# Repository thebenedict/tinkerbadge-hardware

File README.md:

# Tinker Badge hardware

Open **tinkerbadge.kicad_pro** in KiCad 10. The root schematic links to power, processor, display, lighting and peripheral sheets.

- [Specification](docs/spec.md)
- [Current schematic decisions and remaining gates](docs/design/implementation_status.md)
- [Design review, 10 November 2026](docs/design/design_review_2026-11-10.md)
- [Independent review, 11 November 2026](docs/review/design_review_2026-11-11.md) and [the response with the revision 0.3 fixes](docs/review/response_2026-11-11.md)
- [JLCPCB release package and order settings](docs/design/jlcpcb_release.md); order files in `production/jlcpcb/`
- [Reviewed physical-pin assignments](docs/pinouts.md)
- [Verification results](docs/design/verification.md)
- [Planning BOM and source history](docs/AI_Tinkerers_Badge_Design_BOM_Draft_2026-11-09.md)

The first prototype uses a single nominal 3.3 V rail for logic and the eight RGB LEDs. Regulator tolerance can fall below the LED datasheet minimum, so startup, low-battery, radio and full-white load-step tests are required.

This is a development design. The battery is a two-wire protected pouch cell on a rear JST PH header; charging is enabled at about 270 mA with on-board thermistors. The [review response](docs/review/response_2026-11-11.md) lists what changed in board revision 0.3 and what still needs hardware in hand, starting with a dry-fit of the display flex.

## Repeat the electrical check

Export the complete root schematic netlist using KiCad CLI or the installed Konnect MCP, then run:

```
python3 tools/check_schematic_contracts.py path/to/export.net --output path/to/endpoint-result.json
python3 tools/check_schematic_properties.py path/to/export.net --output path/to/property-result.json
python3 tools/test_contract_checker.py
python3 tools/test_property_checker.py
python3 tools/test_alps_buttons.py
```

The checker compares every physical pin and intentional NC with the separately maintained reviewed block contracts. The separate property checker covers explicitly declared values, part numbers, ratings, population and library associations. Run root ERC and inspect fresh sheet renders as well. Current outputs are in `exports/`, with a six-page PDF and a pinned verification manifest. The one-time capture scripts are not idempotent rebuild commands; rerunning them blindly can duplicate objects. Initial electrical capture used Konnect MCP. The user-approved [outlined-block revision](docs/design/outlined_blocks_review.md) uses bounded native edits, independent visual review and complete before/after exported-netlist comparison.

## Licensing

- Original hardware and mechanical designs: **CERN-OHL-P-2.0**.
- Original software, tools and firmware: **Apache-2.0**.
- Original documentation and artwork: **CC-BY-4.0**.

See [the licensing map](LICENSE.md) and [full license texts](LICENSES/README.md). Generated exports retain their source licenses. [Third-party notices](docs/THIRD_PARTY_NOTICES.md) cover KiCad libraries and manufacturer material.

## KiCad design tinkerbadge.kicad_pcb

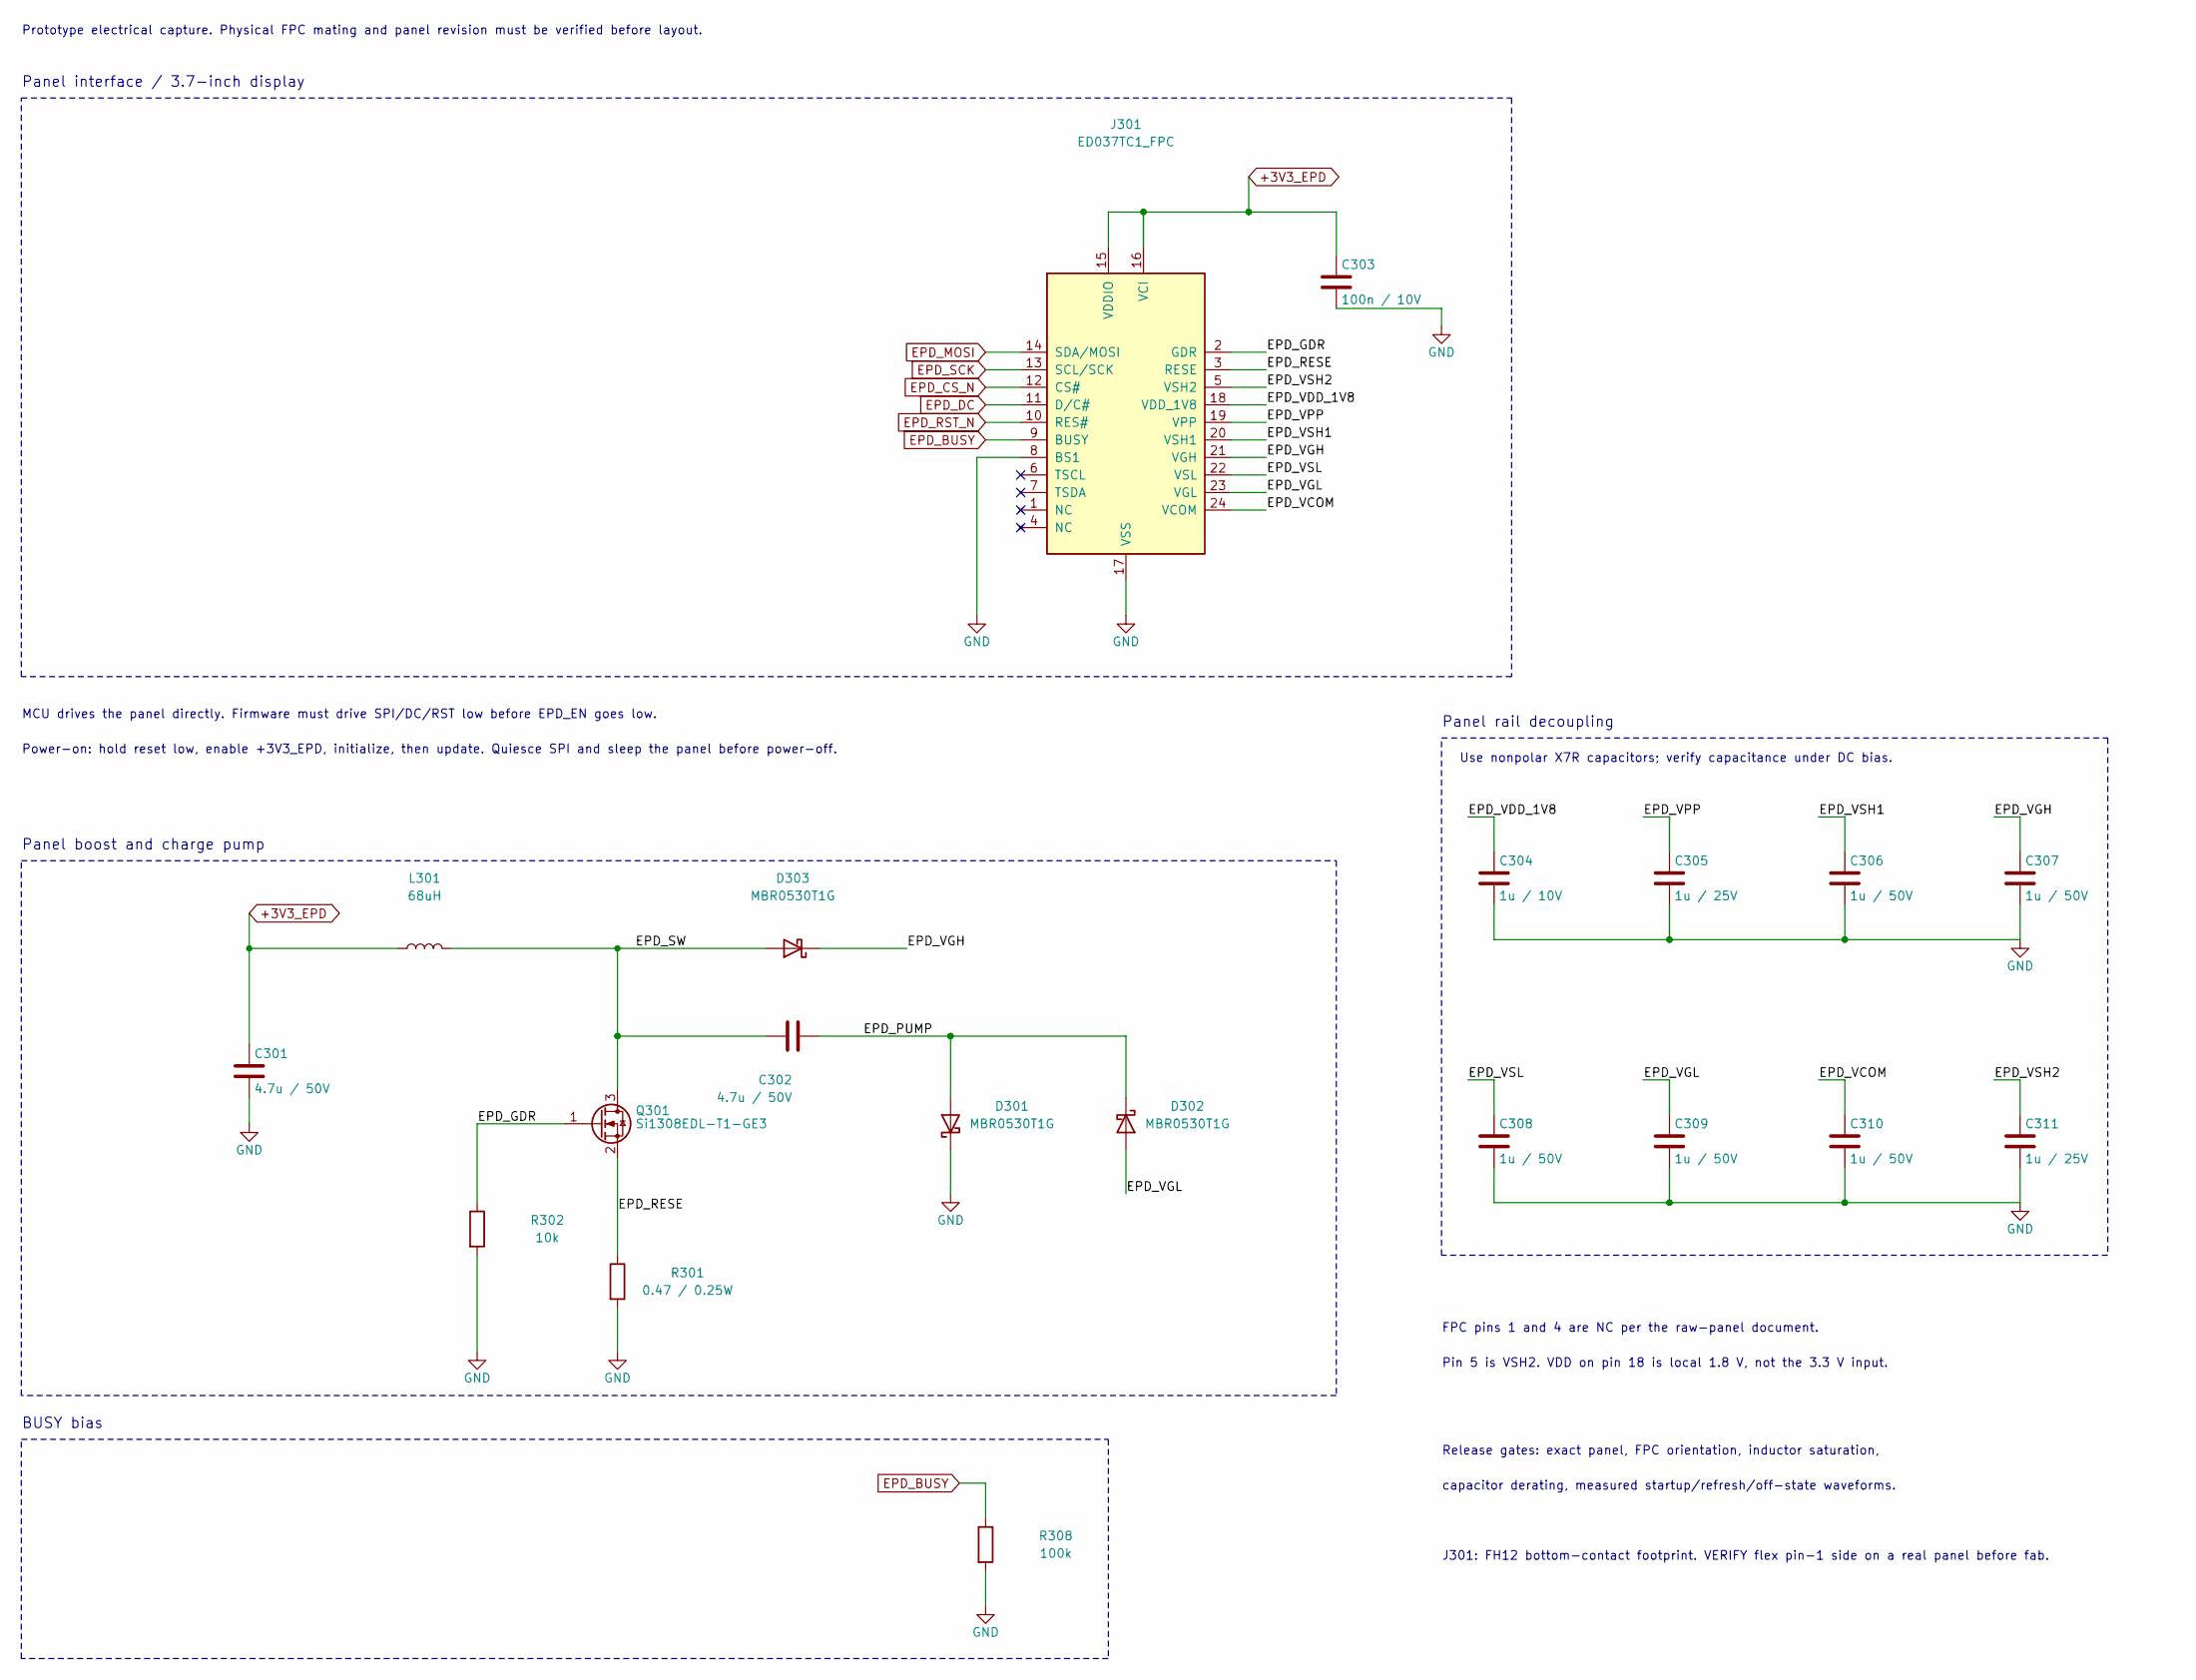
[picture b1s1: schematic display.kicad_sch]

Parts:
C301: 4.7u / 50V; C_1206_3216Metric; Rating 50V; X7R; ±10%; ceramic nonpolar; MPN 1206B475K500NT; LCSC C29823
C302: 4.7u / 50V; C_1206_3216Metric; Rating 50V; X7R; ±10%; ceramic nonpolar; verif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; MPN 1206B475K500NT; LCSC C29823
C303: 100n / 10V; C_0603_1608Metric; Rating 10V; X7R; ±10%; MPN CC0603KRX7R9BB104; LCSC C14663
C304: 1u / 10V; C_0805_2012Metric; Rating 10V; X7R; ±10%; ceramic nonpolar; selec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; MPN CL21B105KBFNNNE; LCSC C28323
C305, C311: 1u / 25V; C_0805_2012Metric; Rating 25V; X7R; ±10%; ceramic nonpolar; selec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; MPN CL21B105KBFNNNE; LCSC C28323
C306, C307, C308, C309, C310: 1u / 50V; C_0805_2012Metric; Rating 50V; X7R; ±10%; ceramic nonpolar; selec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; MPN CL21B105KBFNNNE; LCSC C28323
D301, D302, D303: MBR0530T1G; D_SOD-123; MPN MBR0530T1G; LCSC C82046
J301: ED037TC1_FPC; Hirose_FH12-24S-0.5SH_1x24-1MP_P0.50mm_Horizontal; MPN FH12-24S-0.5SH(55); LCSC C202112
L301: 68uH; L_Bourns-SRN4018; Rating ±20%; shielded; target Isat>=1A and Irm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; MPN SRN4018-680M; LCSC C2041717
Q301: Si1308EDL-T1-GE3; SOT-323_SC-70; MPN SI1308EDL-T1-GE3; LCSC C469327
R301: 0.47 / 0.25W; R_0805_2012Metric; Rating 1%; >=0.25W; pulse-rated; Kelvin route 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; MPN FBF05FT-R470-00L; LCSC C382278
R302: 10k; R_0603_1608Metric; Rating 1%; >=0.1W; MPN 0603WAF1002T5E; LCSC C25804
R308: 100k; R_0603_1608Metric; Rating 1%; >=0.1W; MPN 0603WAF1003T5E; LCSC C25803

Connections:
+3V3_EPD: C301.1, C303.1, J301.15 (VDDIO), J301.16 (VCI), L301.1; also elsewhere on the board
/03 E-PAPER DISPLAY/EPD_GDR: J301.2 (GDR), Q301.1 (G), R302.1
/03 E-PAPER DISPLAY/EPD_PUMP: C302.2, D301.2 (A), D302.1 (K)
/03 E-PAPER DISPLAY/EPD_RESE: J301.3 (RESE), Q301.2 (S), R301.1
/03 E-PAPER DISPLAY/EPD_SW: C302.1, D303.2 (A), L301.2, Q301.3 (D)
/03 E-PAPER DISPLAY/EPD_VCOM: C310.1, J301.24 (VCOM)
/03 E-PAPER DISPLAY/EPD_VDD_1V8: C304.1, J301.18 (VDD_1V8)
/03 E-PAPER DISPLAY/EPD_VGH: C307.1, D303.1 (K), J301.21 (VGH)
/03 E-PAPER DISPLAY/EPD_VGL: C309.1, D302.2 (A), J301.23 (VGL)
/03 E-PAPER DISPLAY/EPD_VPP: C305.1, J301.19 (VPP)
/03 E-PAPER DISPLAY/EPD_VSH1: C306.1, J301.20 (VSH1)
/03 E-PAPER DISPLAY/EPD_VSH2: C311.1, J301.5 (VSH2)
/03 E-PAPER DISPLAY/EPD_VSL: C308.1, J301.22 (VSL)
EPD_BUSY: J301.9 (BUSY), R308.1; also elsewhere on the board
EPD_CS_N: J301.12 (CS#); also elsewhere on the board
EPD_DC: J301.11 (D/C#); also elsewhere on the board
EPD_MOSI: J301.14 (SDA/MOSI); also elsewhere on the board
EPD_RST_N: J301.10 (RES#); also elsewhere on the board
EPD_SCK: J301.13 (SCL/SCK); also elsewhere on the board

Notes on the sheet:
Panel interface / 3.7-inch display
Prototype electrical capture. Physical FPC mating and panel revision must be verified before layout.
MCU drives the panel directly. Firmware must drive SPI/DC/RST low before EPD_EN goes low.
Power-on: hold reset low, enable +3V3_EPD, initialize, then update. Quiesce SPI and sleep the panel before power-off.
Panel boost and charge pump
Panel rail decoupling
Use nonpolar X7R capacitors; verify capacitance under DC bias.
FPC pins 1 and 4 are NC per the raw-panel document.
Pin 5 is VSH2. VDD on pin 18 is local 1.8 V, not the 3.3 V input.
BUSY bias
Release gates: exact panel, FPC orientation, inductor saturation,
capacitor derating, measured startup/refresh/off-state waveforms.
J301: FH12 bottom-contact footprint. VERIFY flex pin-1 side on a real panel before fab.

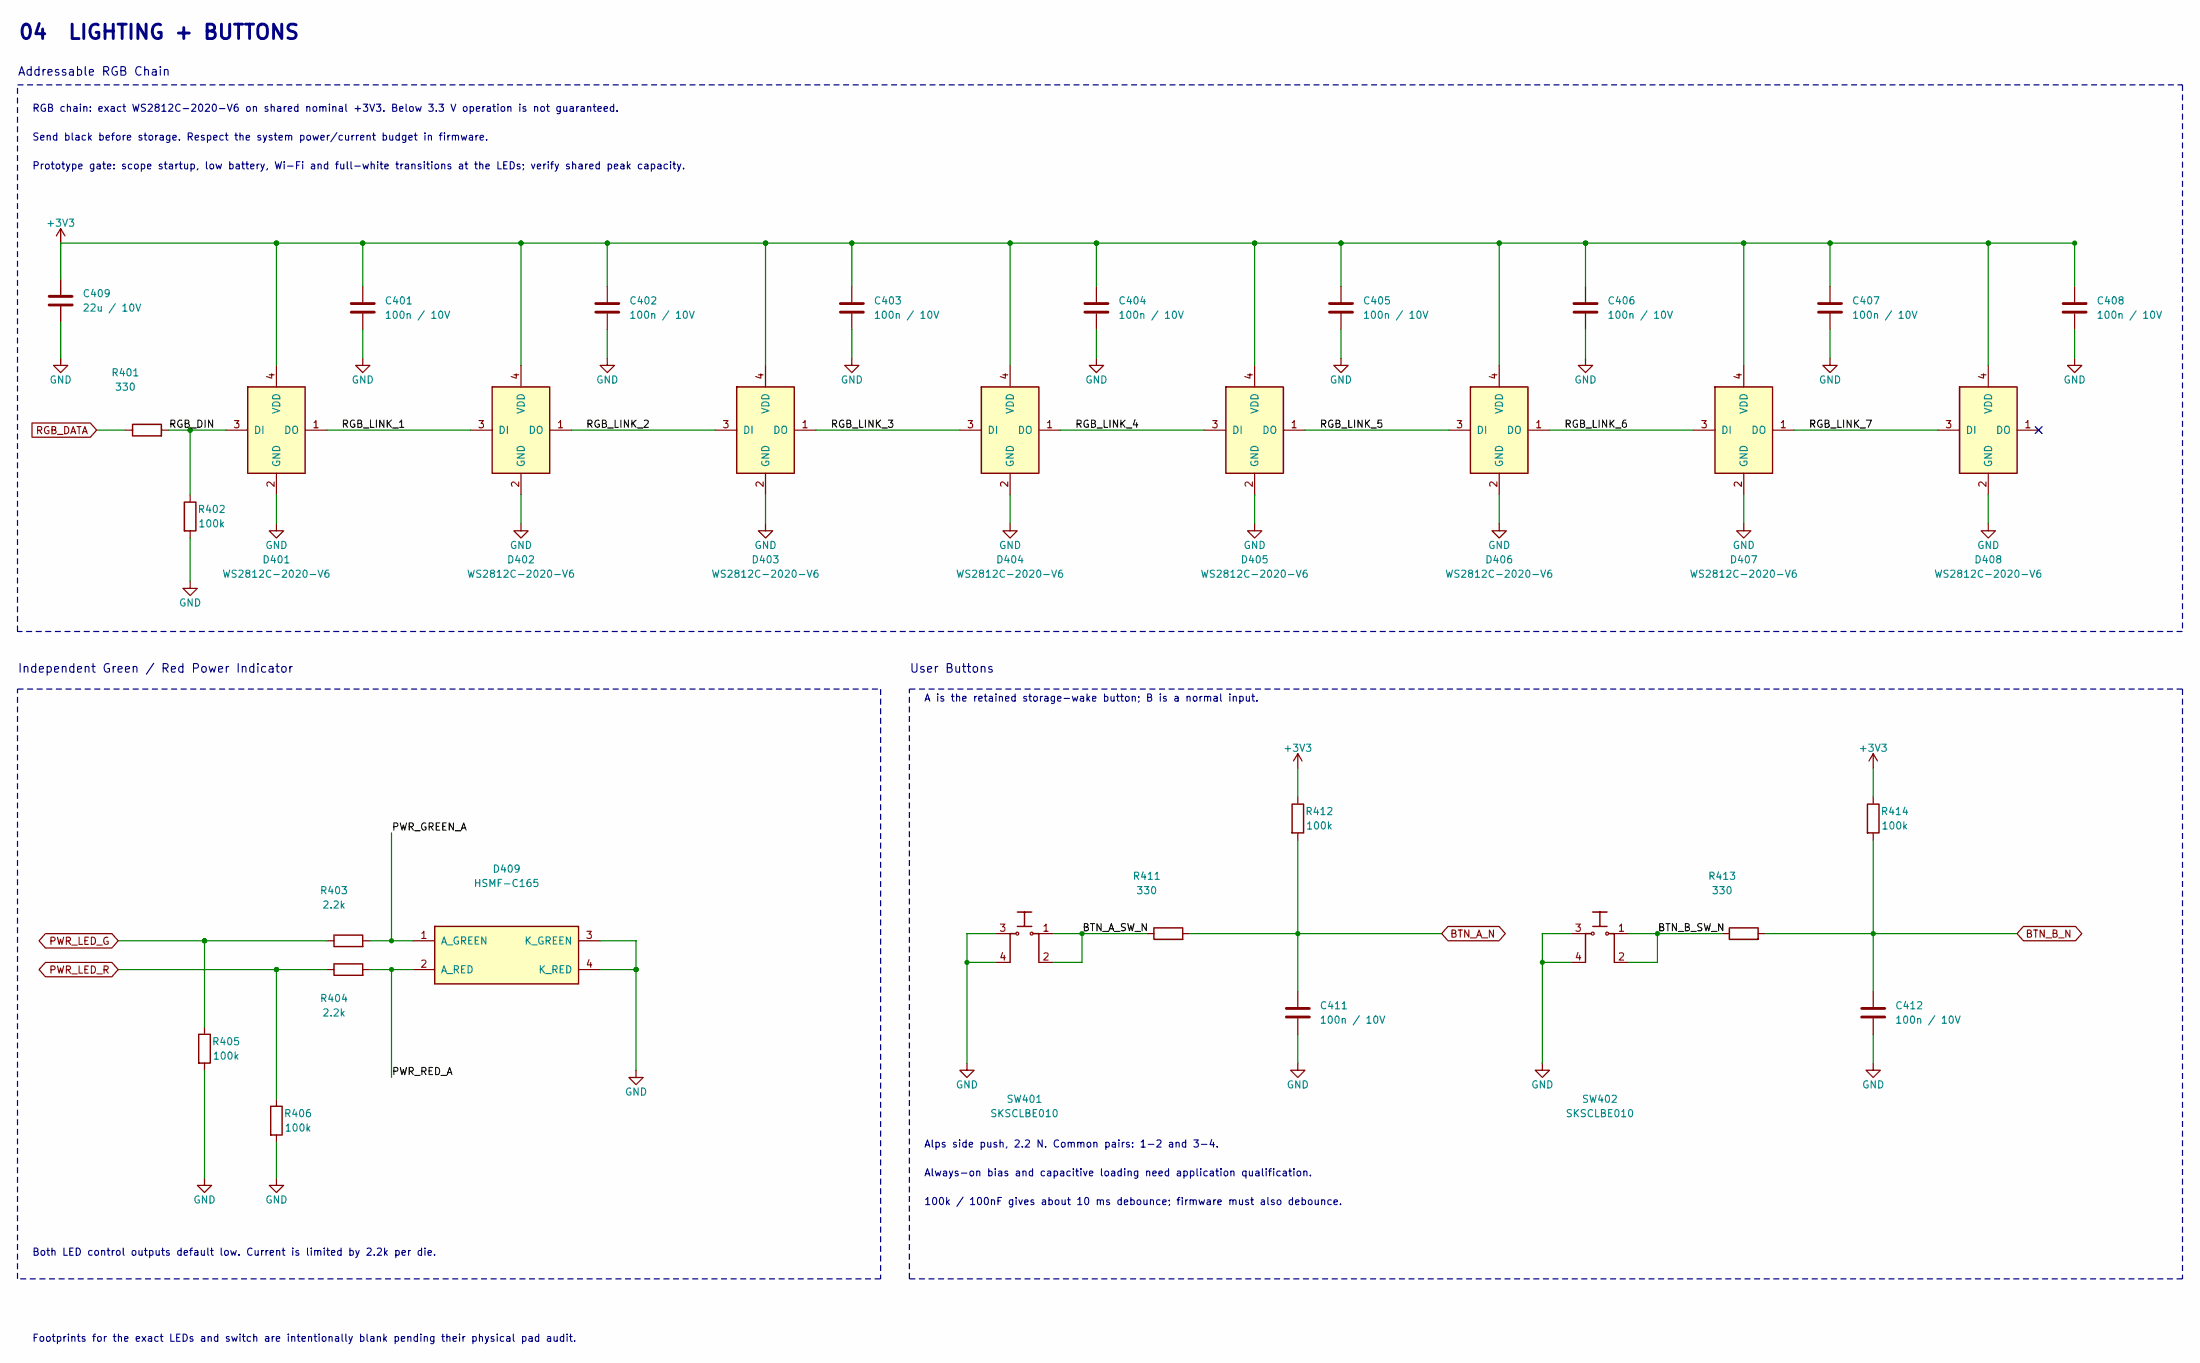
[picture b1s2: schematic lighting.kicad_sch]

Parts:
C401, C402, C403, C404, C405, C406, C407, C408, C411, C412: 100n / 10V; C_0603_1608Metric; Rating 100nF 10V X7R; MPN CC0603KRX7R9BB104; LCSC C14663
C409: 22u / 10V; C_0805_2012Metric; Rating 22uF 10V X7R; MPN CL21A226MAQNNNE; LCSC C45783
D401, D402, D403, D404, D405, D406, D407, D408: WS2812C-2020-V6; WS2812C-2020-V6_Reviewed; Rating 2020 four-pad; MPN WS2812C-2020-V6; LCSC C55109522
D409: HSMF-C165; Rating 0603 four-pad; MPN HSMF-C165; LCSC C188726
R401, R411, R413: 330; R_0603_1608Metric; Rating 330R 1%; MPN 0603WAF3300T5E; LCSC C23138
R402, R405, R406, R412, R414: 100k; R_0603_1608Metric; Rating 100k 1%; MPN 0603WAF1003T5E; LCSC C25803
R403, R404: 2.2k; R_0603_1608Metric; Rating 2.2k 1%; MPN 0603WAF2201T5E; LCSC C4190
SW401, SW402: SKSCLBE010; Rating 12VDC/50mA max;1VDC/10uA min;2.2+/-0.65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; MPN SKSCLBE010; JLCPCB C115361

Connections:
+3V3: C401.1, C402.1, C403.1, C404.1, C405.1, C406.1, C407.1, C408.1, C409.1, D401.4 (VDD), D402.4 (VDD), D403.4 (VDD), D404.4 (VDD), D405.4 (VDD), D406.4 (VDD), D407.4 (VDD), D408.4 (VDD), R412.1, R414.1; also elsewhere on the board
/04 LIGHTING + BUTTONS/BTN_A_SW_N: R411.1, SW401.1, SW401.2
/04 LIGHTING + BUTTONS/BTN_B_SW_N: R413.1, SW402.1, SW402.2
/04 LIGHTING + BUTTONS/PWR_GREEN_A: D409.1 (A_GREEN), R403.2
/04 LIGHTING + BUTTONS/PWR_RED_A: D409.2 (A_RED), R404.2
/04 LIGHTING + BUTTONS/RGB_DIN: D401.3 (DI), R401.2, R402.1
/04 LIGHTING + BUTTONS/RGB_LINK_1: D401.1 (DO), D402.3 (DI)
/04 LIGHTING + BUTTONS/RGB_LINK_2: D402.1 (DO), D403.3 (DI)
/04 LIGHTING + BUTTONS/RGB_LINK_3: D403.1 (DO), D404.3 (DI)
/04 LIGHTING + BUTTONS/RGB_LINK_4: D404.1 (DO), D405.3 (DI)
/04 LIGHTING + BUTTONS/RGB_LINK_5: D405.1 (DO), D406.3 (DI)
/04 LIGHTING + BUTTONS/RGB_LINK_6: D406.1 (DO), D407.3 (DI)
/04 LIGHTING + BUTTONS/RGB_LINK_7: D407.1 (DO), D408.3 (DI)
BTN_A_N: C411.1, R411.2, R412.2; also elsewhere on the board
BTN_B_N: C412.1, R413.2, R414.2; also elsewhere on the board
PWR_LED_G: R403.1, R405.1; also elsewhere on the board
PWR_LED_R: R404.1, R406.1; also elsewhere on the board
RGB_DATA: R401.1; also elsewhere on the board

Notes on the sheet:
04 LIGHTING + BUTTONS
Addressable RGB Chain
Send black before storage. Respect the system power/current budget in firmware.
Independent Green / Red Power Indicator
User Buttons
A is the retained storage-wake button; B is a normal input.
Both LED control outputs default low. Current is limited by 2.2k per die.
100k / 100nF gives about 10 ms debounce; firmware must also debounce.
Footprints for the exact LEDs and switch are intentionally blank pending their physical pad audit.
RGB chain: exact WS2812C-2020-V6 on shared nominal +3V3. Below 3.3 V operation is not guaranteed.
Prototype gate: scope startup, low battery, Wi-Fi and full-white transitions at the LEDs; verify shared peak capacity.
Alps side push, 2.2 N. Common pairs: 1-2 and 3-4.
Always-on bias and capacitive loading need application qualification.

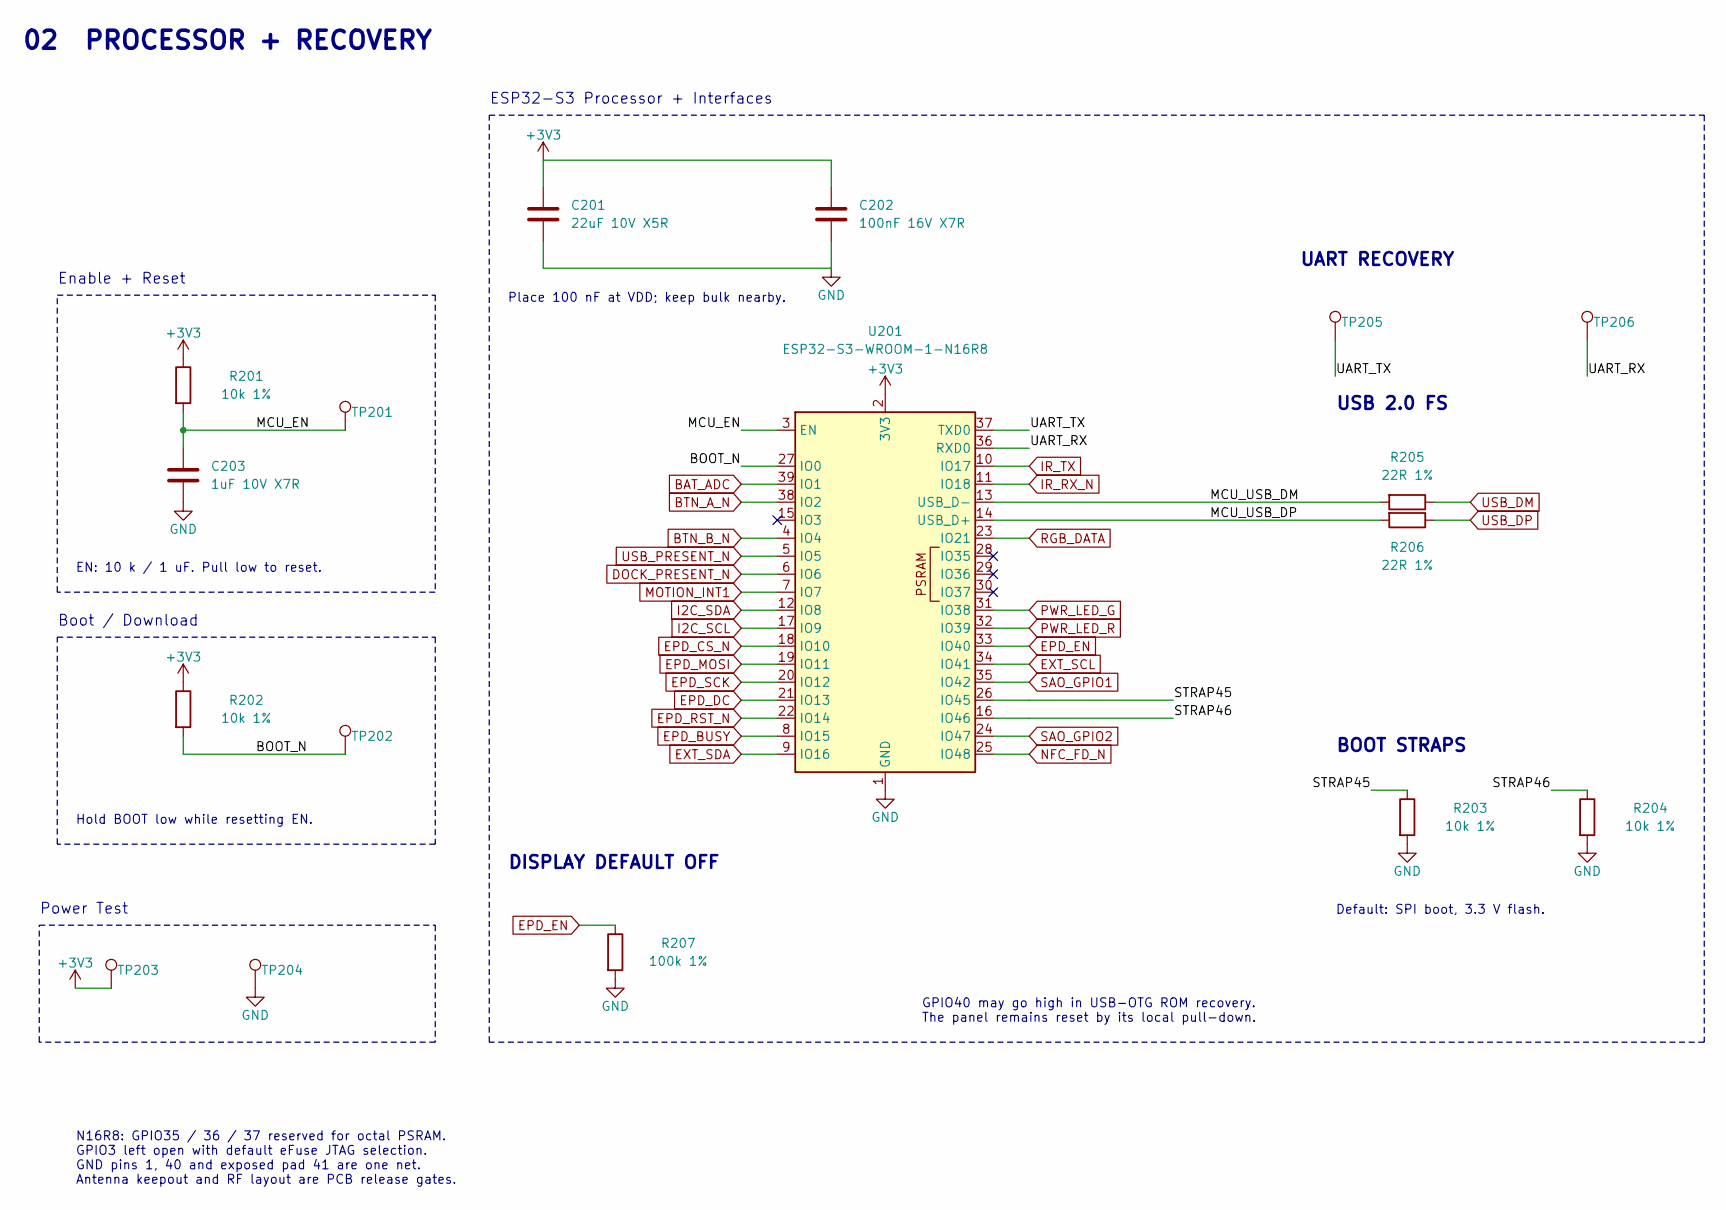
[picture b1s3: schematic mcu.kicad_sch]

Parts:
C201: 22uF 10V X5R; C_0805_2012Metric; MPN CL21A226MAQNNNE; LCSC C45783
C202: 100nF 16V X7R; C_0402_1005Metric; MPN CL05B104KO5NNNC; LCSC C1525
C203: 1uF 10V X7R; C_0402_1005Metric; MPN CL05A105KA5NQNC; LCSC C52923
R201, R202, R203, R204: 10k 1%; R_0402_1005Metric; MPN 0402WGF1002TCE; LCSC C25744
R205, R206: 22R 1%; R_0402_1005Metric; MPN 0402WGF220JTCE; LCSC C25092
R207: 100k 1%; R_0402_1005Metric; MPN 0402WGF1003TCE; LCSC C25741
TP201: MCU_EN; TestPoint_Pad_D1.0mm; MPN PCB pad only: no fitted component
TP202: BOOT_N; TestPoint_Pad_D1.0mm; MPN PCB pad only: no fitted component
TP203: +3V3; TestPoint_Pad_D1.0mm; MPN PCB pad only: no fitted component
TP204: GND; TestPoint_Pad_D1.0mm; MPN PCB pad only: no fitted component
TP205: UART_TX; TestPoint_Pad_D1.0mm; MPN PCB pad only: no fitted component
TP206: UART_RX; TestPoint_Pad_D1.0mm; MPN PCB pad only: no fitted component
U201: ESP32-S3-WROOM-1-N16R8; ESP32-S3-WROOM-1; MPN ESP32-S3-WROOM-1-N16R8; LCSC C2913202

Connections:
+3V3: C201.1, C202.1, R201.1, R202.1, TP203.1, U201.2 (3V3); also elsewhere on the board
/02 PROCESSOR + RECOVERY/BOOT_N: R202.2, TP202.1, U201.27 (IO0)
/02 PROCESSOR + RECOVERY/MCU_EN: C203.1, R201.2, TP201.1, U201.3 (EN)
/02 PROCESSOR + RECOVERY/MCU_USB_DM: R205.2, U201.13 (USB_D-)
/02 PROCESSOR + RECOVERY/MCU_USB_DP: R206.2, U201.14 (USB_D+)
/02 PROCESSOR + RECOVERY/STRAP45: R203.1, U201.26 (IO45)
/02 PROCESSOR + RECOVERY/STRAP46: R204.1, U201.16 (IO46)
/02 PROCESSOR + RECOVERY/UART_RX: TP206.1, U201.36 (RXD0)
/02 PROCESSOR + RECOVERY/UART_TX: TP205.1, U201.37 (TXD0)
BAT_ADC: U201.39 (IO1); also elsewhere on the board
BTN_A_N: U201.38 (IO2); also elsewhere on the board
BTN_B_N: U201.4 (IO4); also elsewhere on the board
DOCK_PRESENT_N: U201.6 (IO6); also elsewhere on the board
EPD_BUSY: U201.8 (IO15); also elsewhere on the board
EPD_CS_N: U201.18 (IO10); also elsewhere on the board
EPD_DC: U201.21 (IO13); also elsewhere on the board
EPD_EN: R207.1, U201.33 (IO40); also elsewhere on the board
EPD_MOSI: U201.19 (IO11); also elsewhere on the board
EPD_RST_N: U201.22 (IO14); also elsewhere on the board
EPD_SCK: U201.20 (IO12); also elsewhere on the board
EXT_SCL: U201.34 (IO41); also elsewhere on the board
EXT_SDA: U201.9 (IO16); also elsewhere on the board
I2C_SCL: U201.17 (IO9); also elsewhere on the board
I2C_SDA: U201.12 (IO8); also elsewhere on the board
IR_RX_N: U201.11 (IO18); also elsewhere on the board
IR_TX: U201.10 (IO17); also elsewhere on the board
MOTION_INT1: U201.7 (IO7); also elsewhere on the board
NFC_FD_N: U201.25 (IO48); also elsewhere on the board
PWR_LED_G: U201.31 (IO38); also elsewhere on the board
PWR_LED_R: U201.32 (IO39); also elsewhere on the board
RGB_DATA: U201.23 (IO21); also elsewhere on the board
SAO_GPIO1: U201.35 (IO42); also elsewhere on the board
SAO_GPIO2: U201.24 (IO47); also elsewhere on the board
USB_DM: R205.1; also elsewhere on the board
USB_DP: R206.1; also elsewhere on the board
USB_PRESENT_N: U201.5 (IO5); also elsewhere on the board

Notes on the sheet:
02 PROCESSOR + RECOVERY
ESP32-S3 Processor + Interfaces
Place 100 nF at VDD; keep bulk nearby.
Enable + Reset
EN: 10 k / 1 uF. Pull low to reset.
Boot / Download
Hold BOOT low while resetting EN.
UART RECOVERY
USB 2.0 FS
BOOT STRAPS
Default: SPI boot, 3.3 V flash.
Power Test
DISPLAY DEFAULT OFF
GPIO40 may go high in USB-OTG ROM recovery. The panel remains reset by its local pull-down.
N16R8: GPIO35 / 36 / 37 reserved for octal PSRAM. GPIO3 left open with default eFuse JTAG selection. GND pins 1, 40 and exposed pad 41 are one net. Antenna keepout and RF layout are PCB release gates.

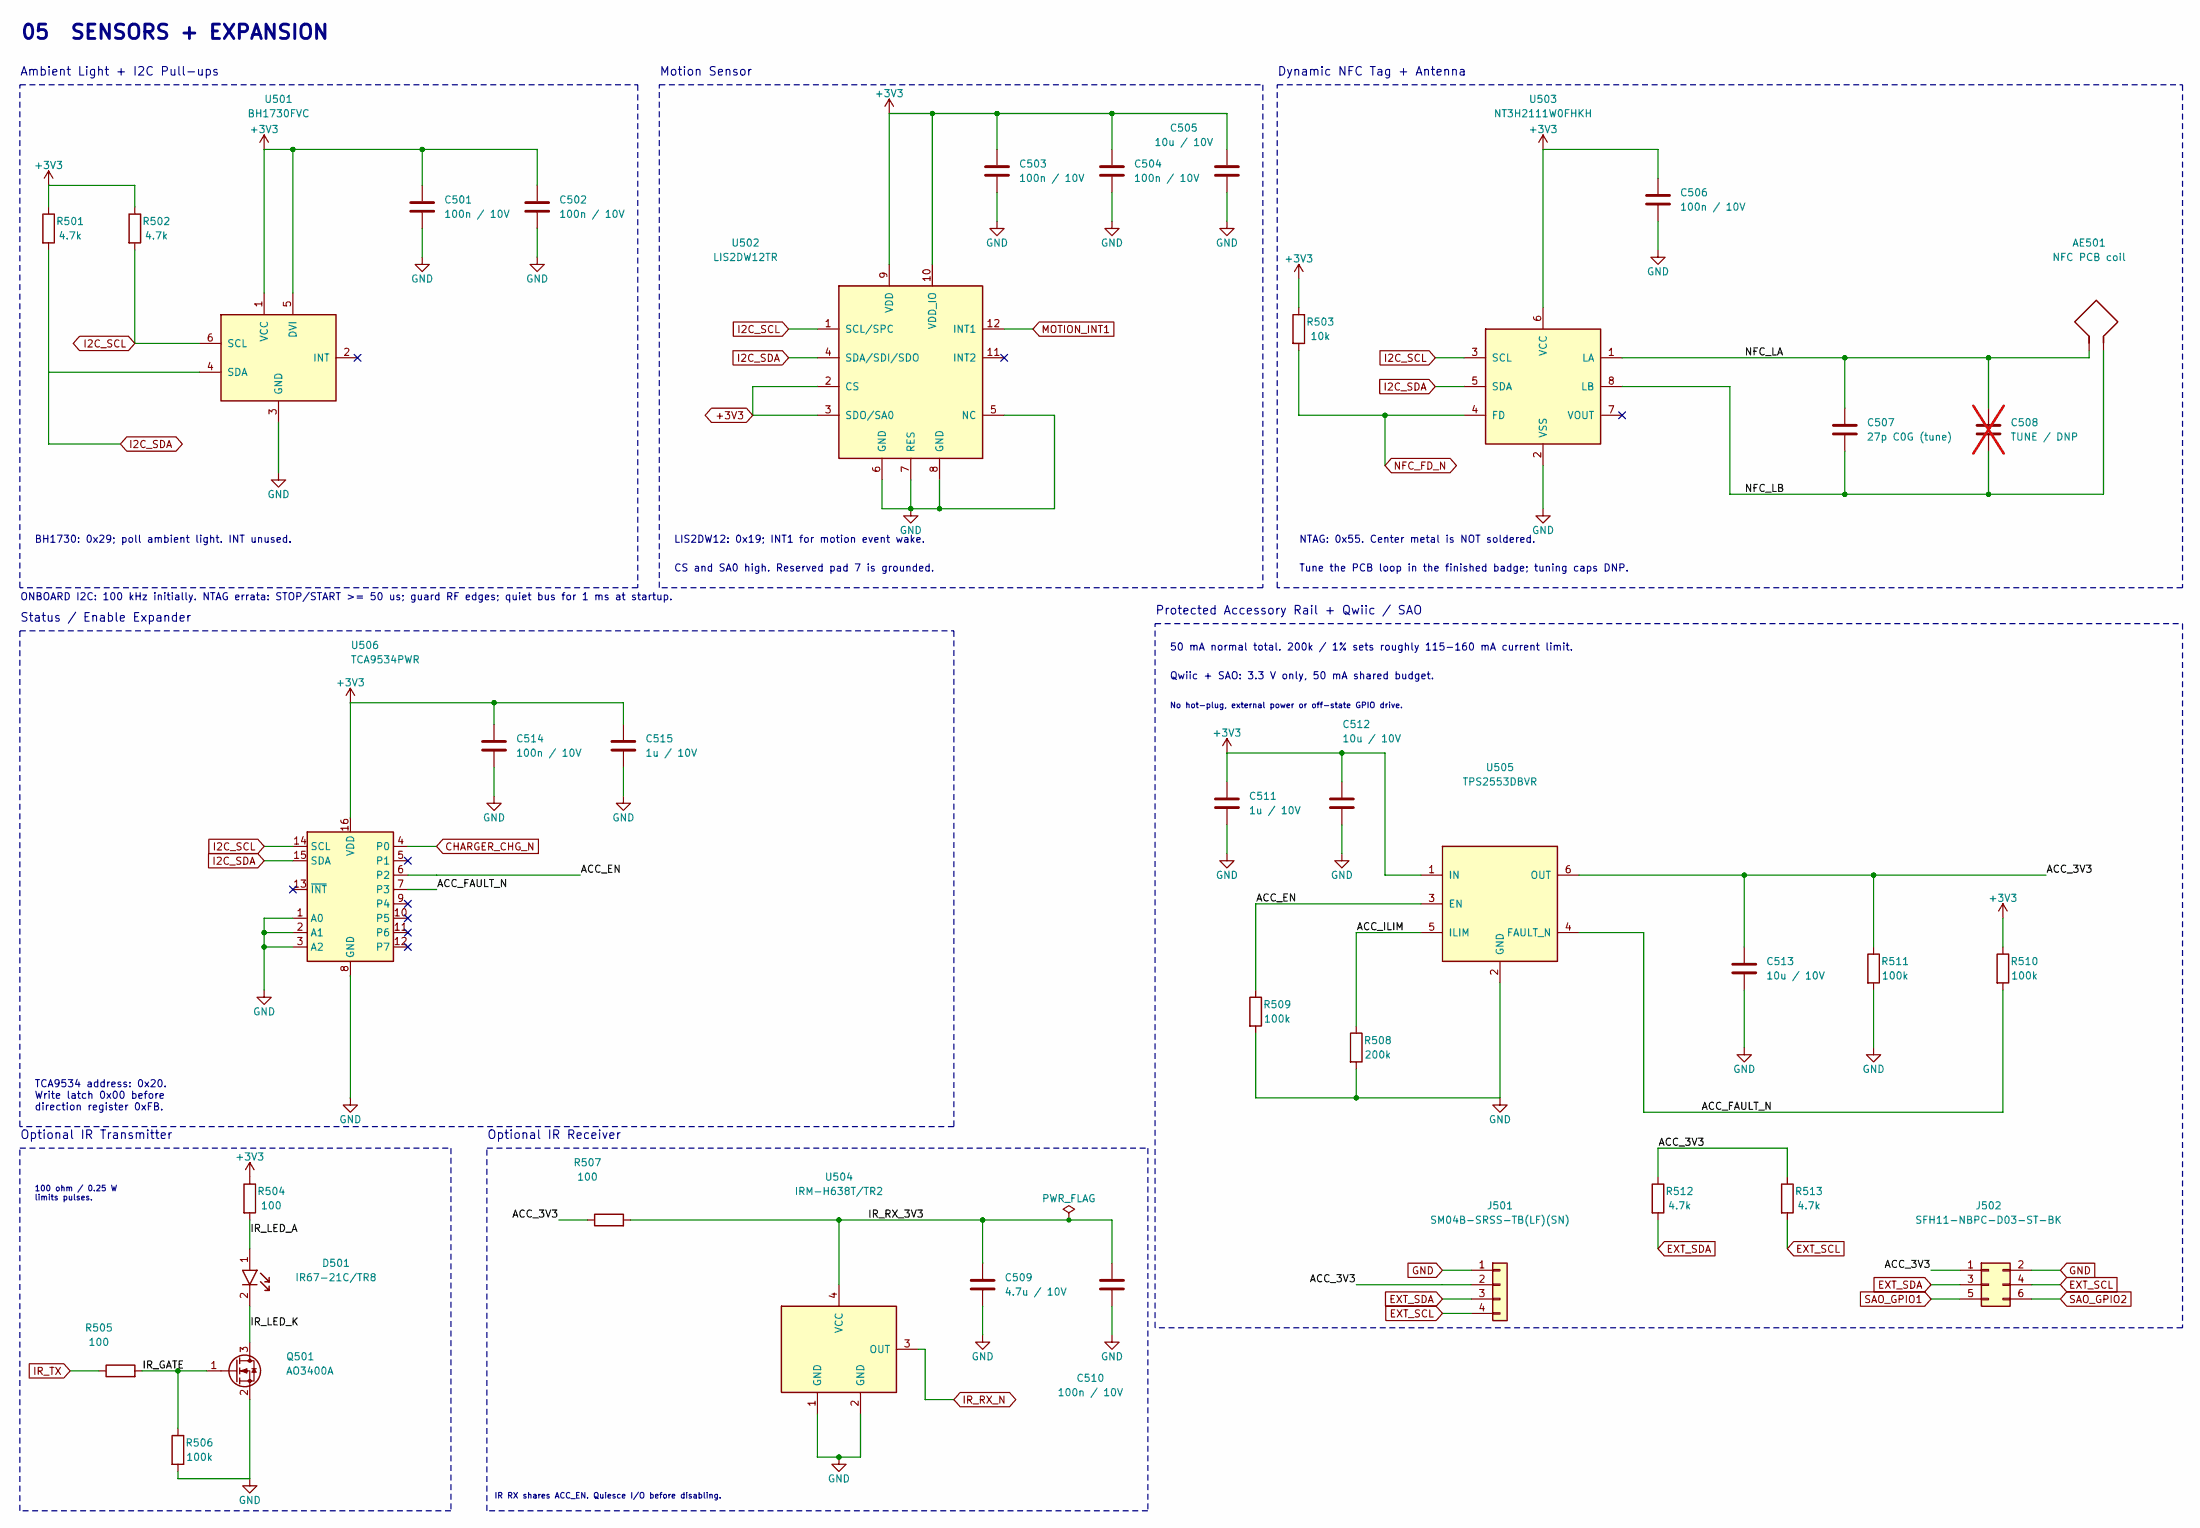
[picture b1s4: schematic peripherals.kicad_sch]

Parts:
AE501: NFC PCB coil; NFC_Coil_Rear_18x13; Rating 13.56MHz PCB loop, tune; MPN PCB feature: no fitted component
C501, C502, C503, C504, C506, C510, C514: 100n / 10V; C_0603_1608Metric; Rating 100nF 10V X7R; MPN CC0603KRX7R9BB104; LCSC C14663
C505, C512, C513: 10u / 10V; C_0805_2012Metric; Rating 10uF 10V X7R; MPN CL21A106KAYNNNE; LCSC C15850
C507: 27p C0G (tune); C_0603_1608Metric; Rating 27p C0G 50V; MPN CC0603JRNPO9BN270; LCSC C107045
C508: TUNE / DNP; C_0603_1608Metric; Rating TUNE DNP C0G 50V; MPN TBD: support part specification; not fitted
C509: 4.7u / 10V; C_0603_1608Metric; Rating 4.7uF 10V X7R; MPN CL10A475KO8NNNC; LCSC C19666
C511, C515: 1u / 10V; C_0603_1608Metric; Rating 1uF 10V X7R; MPN CL10A105KB8NNNC; LCSC C15849
D501: IR67-21C/TR8; IR67-21C_TR8; Rating 3528 two-pad; MPN IR67-21C/TR8; LCSC C60109
J501: SM04B-SRSS-TB(LF)(SN); JST_SH_SM04B_ProjectTabs; Rating SH1x4 side-entry1mm; MPN SM04B-SRSS-TB(LF)(SN); LCSC C160404
J502: SFH11-NBPC-D03-ST-BK; SAO_Socket_2x03_Front; Rating Keyed female2x3 P2.54mm THT; MPN SFH11-NBPC-D03-ST-BK; LCSC C3320727
Q501: AO3400A; SOT-23; Rating SOT-23; MPN AO3400A; LCSC C20917
R501, R502, R512, R513: 4.7k; R_0603_1608Metric; Rating 4.7k 1%; MPN 0603WAF4701T5E; LCSC C23162
R503: 10k; R_0603_1608Metric; Rating 10k 1%; MPN 0603WAF1002T5E; LCSC C25804
R504: 100; R_0805_2012Metric; Rating 100R 1% 0.25W; MPN 0805W8F1000T5E; LCSC C17408
R505, R507: 100; R_0603_1608Metric; Rating 100R 1%; MPN 0603WAF1000T5E; LCSC C22775
R506, R509, R510, R511: 100k; R_0603_1608Metric; Rating 100k 1%; MPN 0603WAF1003T5E; LCSC C25803
R508: 200k; R_0603_1608Metric; Rating 200k 1%; MPN 0603WAF2003T5E; LCSC C25811
U501: BH1730FVC; BH1730FVC_WSOF6; Rating WSOF6; MPN BH1730FVC; LCSC C79616
U502: LIS2DW12TR; LGA-12_2x2mm_P0.5mm; Rating LGA12 2x2mm; MPN LIS2DW12TR; LCSC C189624
U503: NT3H2111W0FHKH; NT3H2111W0FHKH_XQFN8; Rating XQFN8 SOT902-3; MPN NT3H2111W0FHKH; LCSC C710403
U504: IRM-H638T/TR2; IRM-H638T_Reviewed; Rating H6XXT four-pad; MPN IRM-H638T/TR2; LCSC C91447
U505: TPS2553DBVR; SOT-23-6; Rating DBV SOT-23-6; MPN TPS2553DBVR; LCSC C55266
U506: TCA9534PWR; TSSOP-16_4.4x5mm_P0.65mm; Rating PW TSSOP16; MPN TCA9534PWR; LCSC C783615

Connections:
+3V3: C501.1, C502.1, C503.1, C504.1, C505.1, C506.1, C511.1, C512.1, C514.1, C515.1, R501.1, R502.1, R503.1, R504.1, R510.1, U501.1 (VCC), U501.5 (DVI), U502.2 (CS), U502.3 (SDO/SA0), U502.9 (VDD), U502.10 (VDD_IO), U503.6 (VCC), U505.1 (IN), U506.16 (VDD); also elsewhere on the board
/05 SENSORS + EXPANSION/ACC_3V3: C513.1, J501.2, J502.1, R507.1, R511.1, R512.1, R513.1, U505.6 (OUT)
/05 SENSORS + EXPANSION/ACC_EN: R509.1, U505.3 (EN), U506.6 (P2)
/05 SENSORS + EXPANSION/ACC_FAULT_N: R510.2, U505.4 (FAULT_N), U506.7 (P3)
/05 SENSORS + EXPANSION/ACC_ILIM: R508.1, U505.5 (ILIM)
/05 SENSORS + EXPANSION/IR_GATE: Q501.1 (G), R505.2, R506.1
/05 SENSORS + EXPANSION/IR_LED_A: D501.1 (ANODE), R504.2
/05 SENSORS + EXPANSION/IR_LED_K: D501.2 (CATHODE), Q501.3 (D)
/05 SENSORS + EXPANSION/IR_RX_3V3: C509.1, C510.1, R507.2, U504.4 (VCC)
/05 SENSORS + EXPANSION/NFC_LA: AE501.1, C507.1, C508.1, U503.1 (LA)
/05 SENSORS + EXPANSION/NFC_LB: AE501.2, C507.2, C508.2, U503.8 (LB)
CHARGER_CHG_N: U506.4 (P0); also elsewhere on the board
EXT_SCL: J501.4, J502.4, R513.2; also elsewhere on the board
EXT_SDA: J501.3, J502.3, R512.2; also elsewhere on the board
I2C_SCL: R502.2, U501.6 (SCL), U502.1 (SCL/SPC), U503.3 (SCL), U506.14 (SCL); also elsewhere on the board
I2C_SDA: R501.2, U501.4 (SDA), U502.4 (SDA/SDI/SDO), U503.5 (SDA), U506.15 (SDA); also elsewhere on the board
IR_RX_N: U504.3 (OUT); also elsewhere on the board
IR_TX: R505.1; also elsewhere on the board
MOTION_INT1: U502.12 (INT1); also elsewhere on the board
NFC_FD_N: R503.2, U503.4 (FD); also elsewhere on the board
SAO_GPIO1: J502.5; also elsewhere on the board
SAO_GPIO2: J502.6; also elsewhere on the board

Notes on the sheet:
05 SENSORS + EXPANSION
BH1730: 0x29; poll ambient light. INT unused.
LIS2DW12: 0x19; INT1 for motion event wake.
CS and SA0 high. Reserved pad 7 is grounded.
NTAG: 0x55. Center metal is NOT soldered.
Tune the PCB loop in the finished badge; tuning caps DNP.
ONBOARD I2C: 100 kHz initially. NTAG errata: STOP/START >= 50 us; guard RF edges; quiet bus for 1 ms at startup.
Status / Enable Expander
Protected Accessory Rail + Qwiic / SAO
50 mA normal total. 200k / 1% sets roughly 115-160 mA current limit.
TCA9534 address: 0x20. Write latch 0x00 before direction register 0xFB.
Optional IR Transmitter
100 ohm / 0.25 W limits pulses.
Qwiic + SAO: 3.3 V only, 50 mA shared budget.
No hot-plug, external power or off-state GPIO drive.
IR RX shares ACC_EN. Quiesce I/O before disabling.
Ambient Light + I2C Pull-ups
Motion Sensor
Dynamic NFC Tag + Antenna
Optional IR Receiver
